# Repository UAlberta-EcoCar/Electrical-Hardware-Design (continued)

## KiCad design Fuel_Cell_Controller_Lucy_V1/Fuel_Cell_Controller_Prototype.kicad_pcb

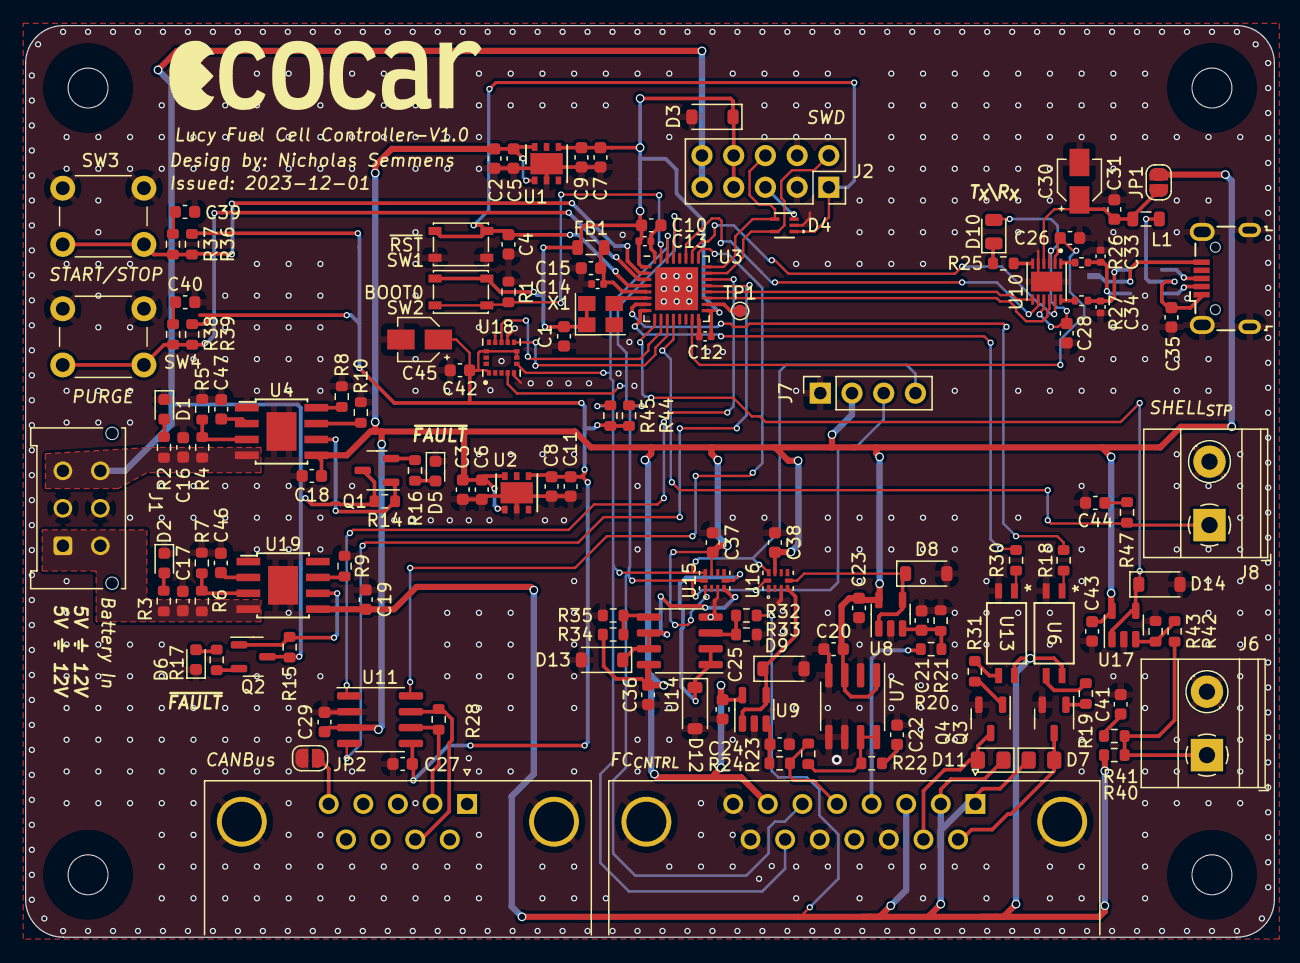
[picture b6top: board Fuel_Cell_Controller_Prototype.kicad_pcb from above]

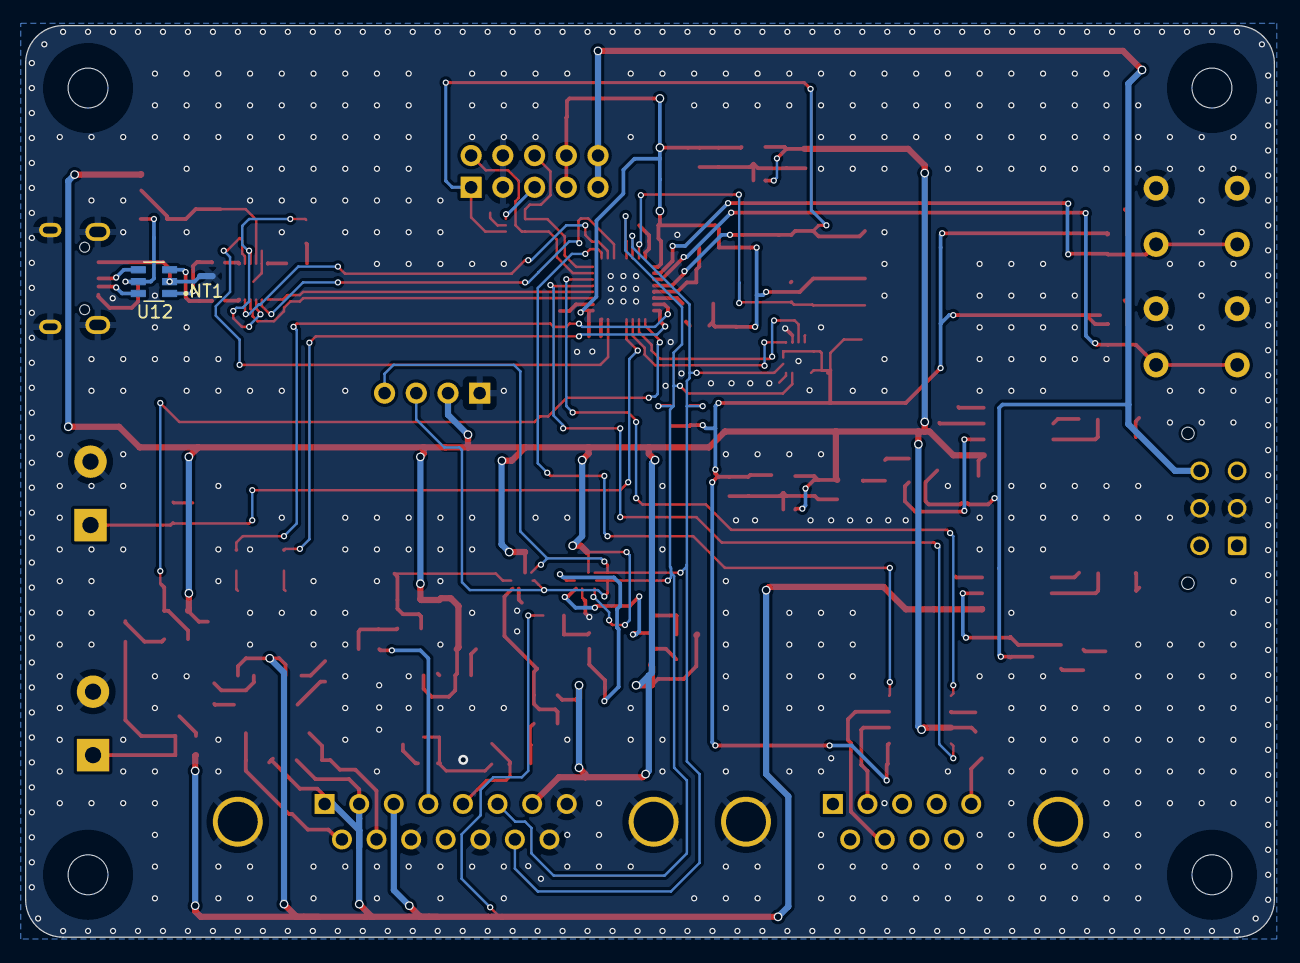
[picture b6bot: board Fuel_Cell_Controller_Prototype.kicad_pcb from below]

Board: 2 copper layers, 100.0 x 73.0 mm, 148 parts (2 on the bottom side), 89 nets.

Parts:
C1, C4, C5, C6, C9, C11, C23, C25, C26, C27, C28, C29, C31, C35, C36, C37, C38, C42, C43: 100n; C_0603_1608Metric
C2, C3, C7, C8, C15, C16, C17, C18, C19, C24: 1u; C_0603_1608Metric
C10: 4u7; C_0603_1608Metric
C12, C13, C14: 100n; C_0402_1005Metric
C20, C22, C39, C40, C41, C44: 2u2; C_0603_1608Metric
C21: 0u33; C_0603_1608Metric
C30: 4u7; CP_Elec_3x5.3
C33, C34: 47p; C_0402_1005Metric
C45: 10u; CP_Elec_3x5.3
C46, C47: 2n2; C_0603_1608Metric
D1, D2: BLUE; LED_0603_1608Metric
D3, D8, D9, D12, D13, D14: MMSZ5226B-7-F; D_SOD_123_M
D4: ESDALC6V1P5
D5, D6: EMERALD; LED_0603_1608Metric
D7, D11: SD0805S020S1R0; D_0805_2012Metric_Pad1.15x1.40mm_HandSolder
D10: PINK; LED_0805_2012Metric
Display 128x64 0.96" I2C: Display_128x64; Display_128x64_096_I2C
FB1: 600R; L_0805_2012Metric
H1, H2, H3, H4: MountingHole; MountingHole_3.2mm_M3
J1: STD_PWR_HEADER
J2: Conn_02x05_Odd_Even; PinSocket_2x05_P2.54mm_Vertical
J3: DE9_Receptacle; DSUB-9_Female_Horizontal_P2.77x2.84mm_EdgePinOffset7.70mm_H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
J4: DA15_Receptacle_MountingHoles; DSUB-15_Female_Horizontal_P2.77x2.84mm_EdgePinOffset7.70mm_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
J5: USB_B_Micro; USB_Micro-B_Wuerth_629105150521
J6, J8: Screw_Terminal_01x02; TerminalBlock_Phoenix_MKDS-1,5-2-5.08_1x02_P5.08mm_Horizont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
J7: OLED; PinSocket_1x04_P2.54mm_Vertical
JP1, JP2: SolderJumper_2_Open; SolderJumper-2_P1.3mm_Open_RoundedPad1.0x1.5mm
L1: 600R/0.5A; L_0805_2012Metric
NT1: NetTie_2; NetTie-2_SMD_Pad0.5mm
Q1, Q2: SI2302A-TPMSCT-ND; SOT-23-3
Q3, Q4: FMMT491ATA; SOT-23-3
R1, R5, R7, R24, R36, R37, R38, R39, R40, R41, R47: 10k; R_0603_1608Metric
R2, R16, R17: 270; R_0603_1608Metric
R3, R43: 820; R_0603_1608Metric
R4: 11k; R_0603_1608Metric
R6: 900; R_0603_1608Metric
R8: 400k; R_0603_1608Metric
R9, R10: 1k; R_0603_1608Metric
R14, R15, R23: 100k; R_0603_1608Metric
R18, R30: 422; R_0603_1608Metric
R19, R31: 249; R_0603_1608Metric
R20: 6.8k; R_0603_1608Metric
R21, R33, R34, R35: 13k; R_0603_1608Metric
R22, R25: 51; R_0603_1608Metric
R26, R27: 33; R_0402_1005Metric
R28: 120; R_0603_1608Metric
R32: 51k; R_0603_1608Metric
R42: 2.2k; R_0603_1608Metric
R44, R45: 4.7k; R_0603_1608Metric
SW1, SW2: PTS815 SJM 250 SMTR LFS; SW_SPST_PTS810
SW3, SW4: SW_PUSH_6mm_H5mm
TP1: MCO; TestPoint_Pad_D1.0mm
U1, U2: LD39050PU33R; DFN-6-1EP_3x3mm_P0.95mm_EP1.7x2.6mm
U3: STM32L432KCUx; QFN-32-1EP_5x5mm_P0.5mm_EP3.45x3.45mm
U4, U19: TPS259621; TI_SO-PowerPAD-8
U6, U13: EL3H7(B)(TA)-VG; SOIC_BTA-VG_EVS
U7: MCP1501-33E/SN; SOIC-8_3.9x4.9mm_P1.27mm
U8, U9, U17: AD8603; TSOT-23-5
U10: FT234XD-R; SON45P300X300X80-13N
U11: MCP2542FD-E/SN; SOIC-8_3.9x4.9mm_P1.27mm
U12: USBLC6-2SC6
U14: MCP602-E/SN; SOIC-8_3.9x4.9mm_P1.27mm
U15, U16: ADS1115IRUGR; IC_ADS1115IRUGR
U18: LIS3DHTR; XDCR_LIS3DHTR
X1: OXETDLJANF-8MHZ; Crystal_SMD_3225-4Pin_3.2x2.5mm

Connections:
+3V3: C8.2, C11.2, C27.1, C42.2, C45.1, R37.2, R38.2, R44.2, R45.2, U2.4 (VO), U11.5 (VIO), U18.1 (VDD_IO), U18.7 (SDO/SA0), U18.8 (CS), U18.14 (VDD)
+5V: C2.2, C3.2, C5.2, C6.2, C18.2, C20.1, C23.2, C25.2, C29.2, C36.2, C37.2, C38.2, C43.2, J4.7, J7.2, JP1.2 (B), R34.1, U1.1 (EN), U1.6 (VI), U2.1 (EN), U2.6 (VI), U4.5 (OUT), U7.1 (VDD), U7.3 (~SHDN), U8.5 (V+), U9.5 (V+), U11.3 (VDD), U14.8 (V+), U15.1 (ADDR), U15.8 (VDD), U16.8 (VDD), U17.5 (V+)
+12V: C19.2, D7.1 (K), D11.1 (K), J4.1, J4.2, J4.3, R32.1, R40.1, U6.4, U13.4, U19.5 (OUT)
/BOOT0: R1.2, SW2.1, U3.31 (PH3)
/BTN_{1}: R36.2, R37.1, SW3.2, U3.2 (PC14)
/BTN_{2}: R38.1, R39.2, SW4.2, U3.3 (PC15)
/FLT_{5}: Q1.1 (G), R14.1, U4.6 (~FAULT)
/FLT_{12}: Q2.1 (G), R15.1, U19.6 (~FAULT)
/IO /BTN_{RTN}: J6.1, R40.2, R41.1, R42.2
/IO /CAN_H: J3.7, R28.2, U11.7 (CANH)
/IO /CAN_L: J3.2, R28.1, U11.6 (CANL)
/IO /D+: J5.3 (D+), U12.4
/IO /D-: J5.2 (D-), U12.6
/IO /DM: C33.1, R26.2, U12.1
/IO /DP: C34.1, R27.2, U12.3
/IO /FC_{TEMP}: D9.1, U9.1, U9.4 (-), U16.4 (AIN0)
/IO /GND_{1}: J5.5 (GND), NT1.2, U12.2
/IO /H2_{PRS}: D8.1, U8.1, U8.4 (-), U16.5 (AIN1)
/IO /PA0: U3.6 (PA0), X1.3 (OUT)
/IO /PA1: R18.2, U3.7 (PA1)
/IO /PA2: R30.2, U3.8 (PA2)
/IO /PA3: D14.1, U3.9 (PA3), U17.1, U17.4 (-)
/IO /PA4: U3.10 (PA4), U18.11 (INT1)
/IO /PA5: U3.11 (PA5), U18.9 (INT2)
/IO /PA6: J8.1, R47.1, U3.12 (PA6)
/IO /PA8: TP1.1, U3.18 (PA8)
/IO /PA9: U3.19 (PA9), U10.10 (RXD)
/IO /PA10: U3.20 (PA10), U10.7 (TXD)
/IO /PA11: U3.21 (PA11), U11.4 (RXD)
/IO /PA12: U3.22 (PA12), U11.1 (TXD)
/IO /PA13: D4.5, J2.2, U3.23 (PA13)
/IO /PA14: D4.4, J2.6, U3.24 (PA14)
/IO /PA15: U3.25 (PA15), U11.8 (STBY)
/IO /PB1: C26.2, U3.15 (PB1), U10.2 (~RESET#)
/IO /PB3: U3.26 (PB3), U10.11 (CTS#)
/IO /PB4: U3.27 (PB4), U10.8 (RTS#)
/IO /PB6: J4.6, J7.3, R44.1, U3.29 (PB6), U15.10 (SCL), U16.10 (SCL), U18.4 (SCL/SPC)
/IO /PB7: J4.14, J7.4, R45.1, U3.30 (PB7), U15.9 (SDA), U16.9 (SDA), U18.6 (SDA/SDI/SDO)
/IO /PRESSURE_SIG: J4.4, R20.2
/IO /PURGE_RTN: D11.2 (A), J4.10, Q4.3 (C)
/IO /Purge_Valve_Switch/V_{E}: R31.1, U13.3
/IO /SHIELD: J3.5, JP2.2 (B)
/IO /SUPPLY_RTN: D7.2 (A), J4.9, Q3.3 (C)
/IO /Supply_Valve_Switch/V_{E}: R19.1, U6.3
/IO /THERM_{VREF}: J4.5, R23.2, R24.2
/IO /VCCIO: C28.1, D10.2 (A), U10.3 (3V3OUT), U10.9 (VCCIO)
/IO /V_{BUS}: C35.1, J5.1 (VBUS), L1.2, U12.5
/MCU_3V3: C1.1, C7.2, C9.2, C10.1, C12.1, C13.1, D3.1, FB1.1, J2.7, J2.8, SW2.2, U1.4 (VO), U3.1 (VDD), U3.17 (VDD), X1.1 (Tri-State), X1.4 (VDD)
/On-Board Sensors/5V_{REF}: D13.1, U14.6 (-), U14.7, U15.4 (AIN0)
/On-Board Sensors/12V_{REF}: D12.1, U14.1, U14.2 (-), U15.5 (AIN1)
/SW_{IM}: D4.3, J2.5
/~RST: C4.1, D4.1, J2.1, SW1.2, U3.4 (NRST)
GNDA: C1.2, C2.1, C3.1, C4.2, C5.1, C6.1, C7.1, C8.1, C9.1, C10.2, C11.1, C12.2, C13.2, C14.2, C15.2, C16.1, C17.1, C18.1, C19.1, C20.2, C21.2, C22.2, C23.1, C24.2, C25.1, C26.1, C27.2, C28.2, C29.1, C30.2, C31.2, C33.2, C34.2, C35.2, C36.1, C37.1, C38.1, C39.2, C40.2, C41.2, C42.1, C43.1, C44.2, C45.2, C46.1, C47.1, D1.1 (K), D2.1 (K), D3.2, D4.2, D5.1 (K), D6.1 (K), D8.2, D9.2, D12.2, D13.2, D14.2, J1.2 (GND), J1.5 (GND), J2.3, J2.4, J3.0 (PAD), J4.0 (PAD), J4.8, J4.11 (P111), J4.13, J4.15, J5.6 (Shield), J6.2, J7.1, J8.2, JP2.1 (A), NT1.1, Q3.2 (E), Q4.2 (E), R1.1, R5.1, R7.1, R8.1, R9.1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
unnamed: C22.1, R22.2
unnamed: C39.1, R36.1
unnamed: C40.1, R39.1
unnamed: C41.1, R41.2
unnamed: C44.1, R47.2
unnamed: D1.2 (A), R2.1
unnamed: D2.2 (A), R3.1
unnamed: D5.2 (A), R16.1
unnamed: D6.2 (A), R17.1
unnamed: D10.1 (K), R25.1
unnamed: C30.1, C31.1, JP1.1 (A), L1.1, U10.4 (VCC)
unnamed: Q1.2 (S), R16.2
unnamed: Q2.2 (S), R17.2
unnamed: Q3.1 (B), R19.2
unnamed: Q4.1 (B), R31.2
unnamed: R18.1, U6.1
unnamed: R30.1, U13.1
unnamed: C14.1, C15.1, FB1.2, U3.5 (VDDA)
unnamed: R4.1, R5.2, U4.3 (EN/UVLO)
unnamed: R10.2, U4.7 (ILM)
unnamed: R8.2, U4.8 (OVLO)
unnamed: C47.2, U4.2 (dV/dT)
unnamed: R22.1, R23.1, U7.7 (OUT), U7.8 (FB)
unnamed: C21.1, R20.1, R21.1, U8.3 (+)
unnamed: C24.1, R24.1, U9.3 (+)
unnamed: R25.2, U10.6 (CBUS0)
unnamed: R26.1, U10.1 (USBDM)
unnamed: R27.1, U10.12 (USBDP)
unnamed: R32.2, R33.1, U14.3 (+)
unnamed: R34.2, R35.1, U14.5 (+)
unnamed: R42.1, R43.1, U17.3 (+)
unnamed: R6.1, R7.2, U19.3 (EN/UVLO)
unnamed: R9.2, U19.7 (ILM)
unnamed: C46.2, U19.2 (dV/dT)
UNPROTECTED_5V: C16.2, J1.3 (5V), J1.6 (5V), J2.9, J2.10, Q1.3 (D), Q2.3 (D), R2.2, R4.2, R14.2, R15.2, U4.4 (IN)
UNPROTECTED_12V: C17.2, J1.1 (12V), J1.4 (12V), R3.2, R6.2, U19.4 (IN)

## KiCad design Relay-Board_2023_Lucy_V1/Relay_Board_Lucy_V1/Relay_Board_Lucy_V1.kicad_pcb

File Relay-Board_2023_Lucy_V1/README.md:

#I'm not quite sure how these documents work yet but im excited to find out

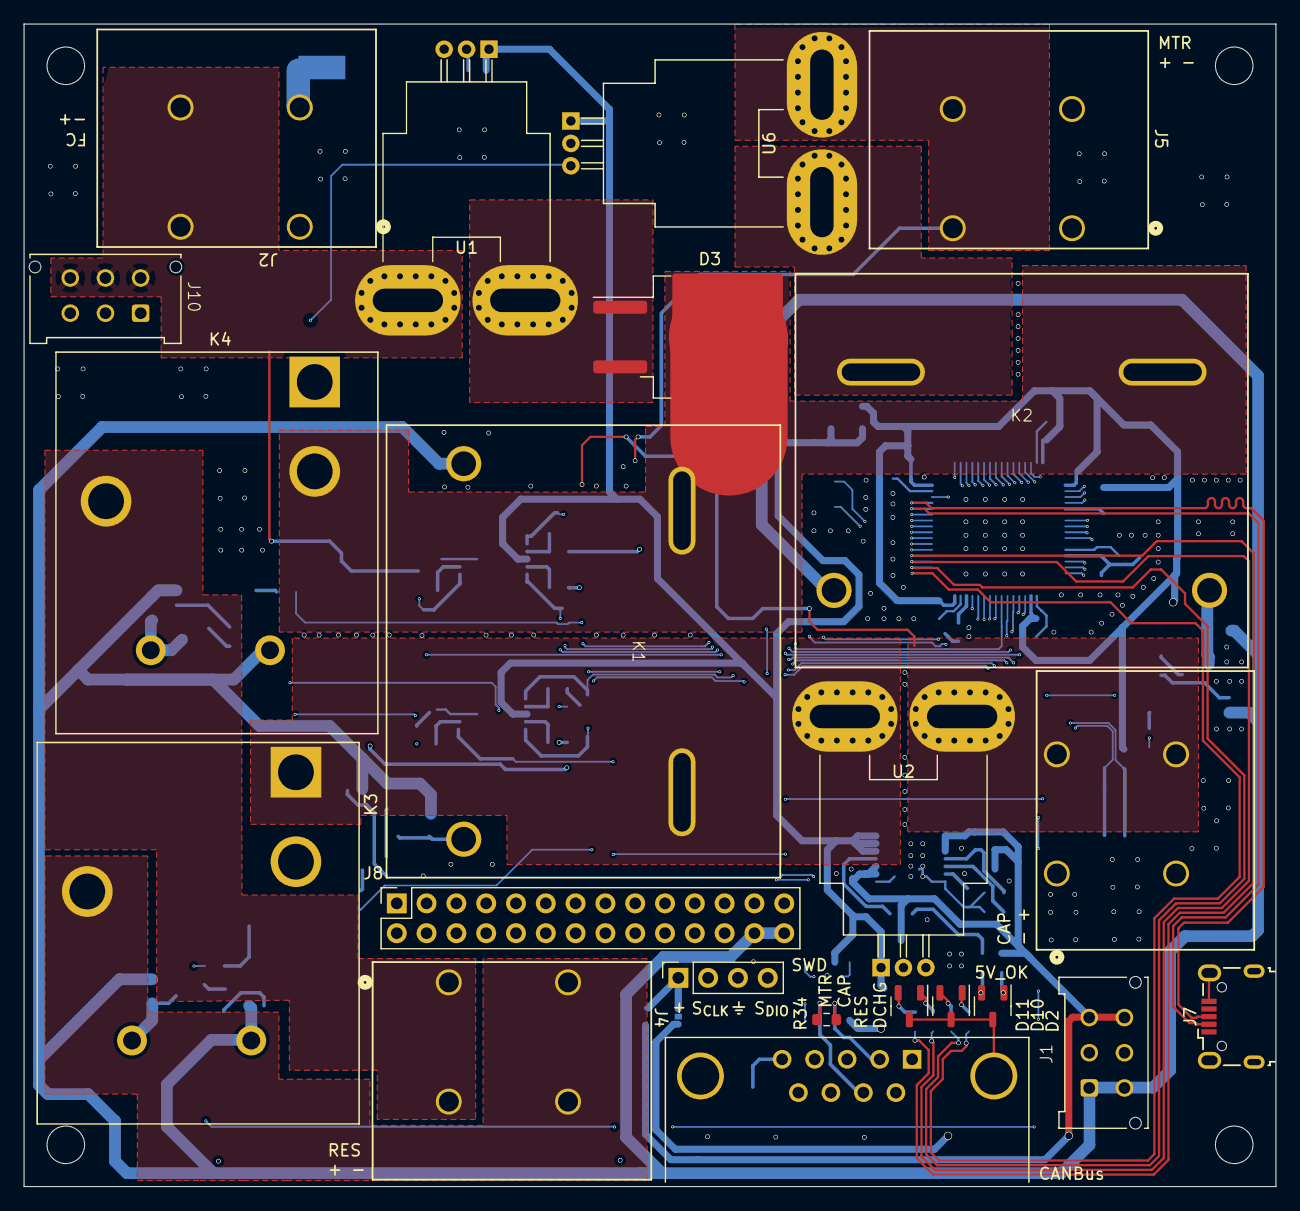
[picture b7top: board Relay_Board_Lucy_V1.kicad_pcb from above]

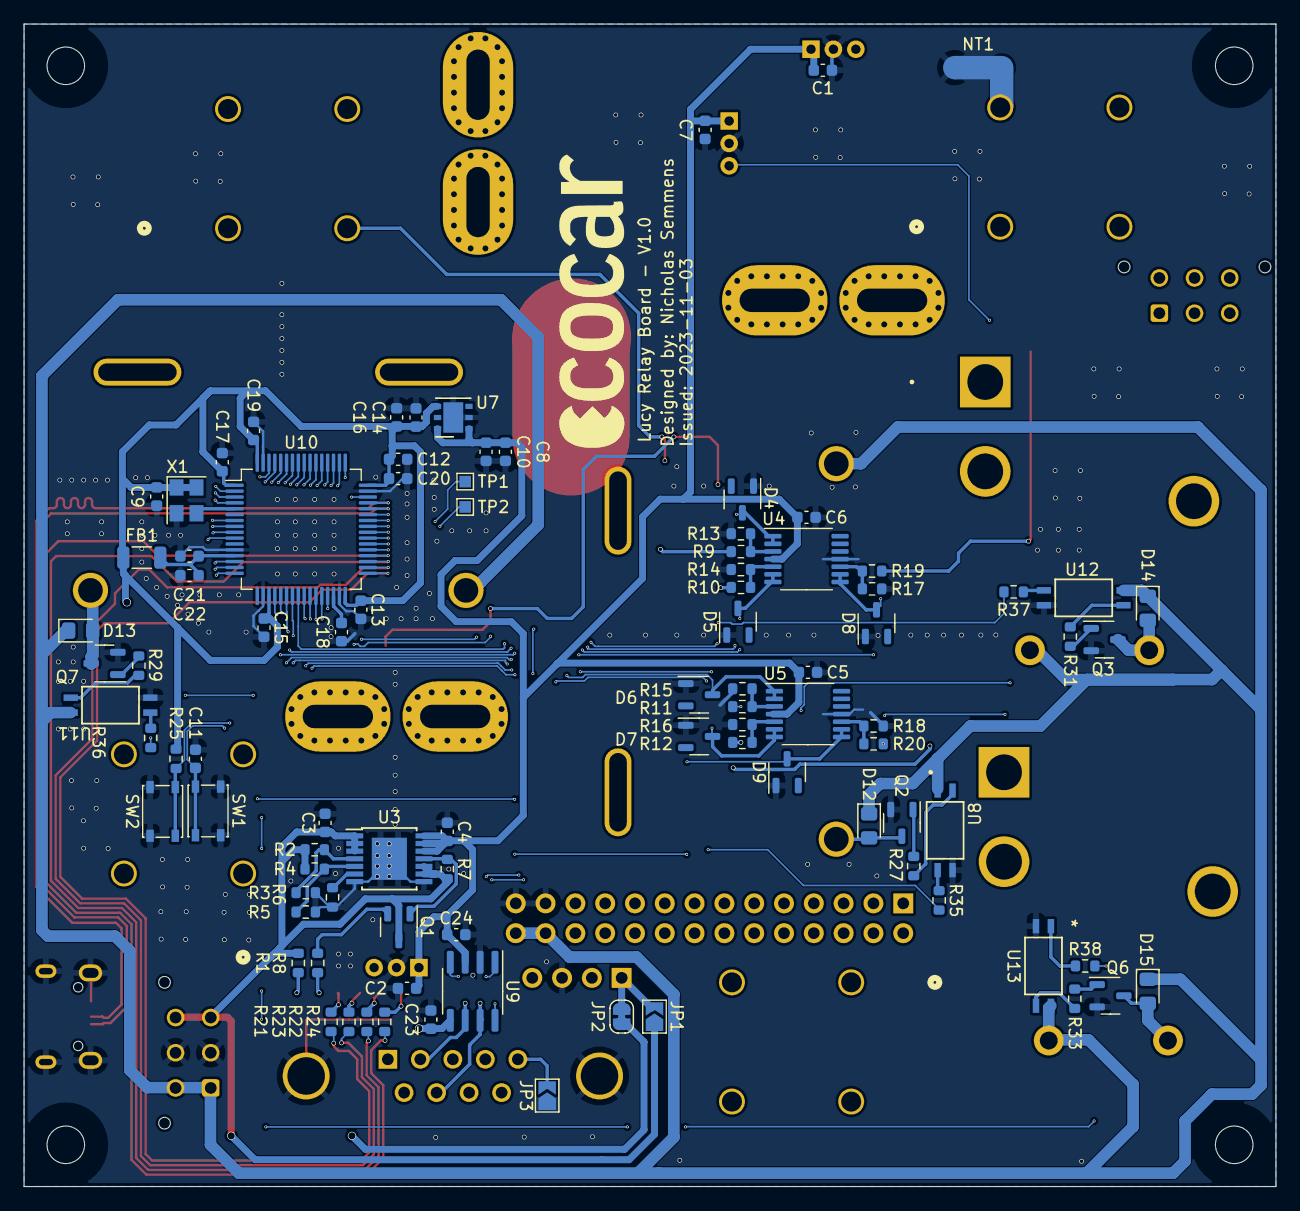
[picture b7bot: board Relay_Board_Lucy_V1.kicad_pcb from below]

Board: 4 copper layers, 106.7 x 99.1 mm, 118 parts (92 on the bottom side), 106 nets.

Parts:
C1, C2, C5, C6, C7, C9, C10, C11, C13, C15, C16, C17, C19, C20, C21, C23, C24: 100n; C_0603_1608Metric
C3, C4, C8, C14, C22: 1u; C_0603_1608Metric
C12, C18: 4u7; C_0603_1608Metric
D2, D10, D11: AM23ESGW; SOT-23-3
D3: STPS5045SG-TR; TO-263-2
D4, D5, D6, D7, D8, D9: BZX84-C3V3,215; SOT-23-3
D12, D13, D14, D15: SD0805S020S1R0; D_0805_2012Metric_Pad1.15x1.40mm_HandSolder
FB1: 300R; L_1206_3216Metric
H1, H2, H3, H4: MountingHole; MountingHole_3.2mm_M3
J1, J10: STD_PWR_HEADER
J2, J3, J4, J5: VP0265540000G; CONN_VP0265x4xxxxG_AMP
J6: SWD_HEADER; PinSocket_1x04_P2.54mm_Vertical
J7: USB_B_Micro; USB_Micro-B_Wuerth_629105150521
J8: Conn_02x14_Top_Bottom; PinSocket_2x14_P2.54mm_Vertical
J9: DE9_Receptacle_MountingHoles; DSUB-9_Female_Horizontal_P2.77x2.84mm_EdgePinOffset7.70mm_H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
JP1, JP3: SolderJumper_2_Open; SolderJumper-2_P1.3mm_Open_TrianglePad1.0x1.5mm
JP2: SolderJumper_2_Bridged; SolderJumper-2_P1.3mm_Bridged_RoundedPad1.0x1.5mm
K1, K2: HE1AN-P-DC12V-Y5
K3, K4: J115F11CH12VDCS61.5
NT1: NetTie_2; NetTie-2_SMD_Pad2.0mm
Q1: SI2302A-TPMSCT-ND; SOT-23-3
Q2, Q3, Q6, Q7: FMMT491ATA; SOT-23-3
R1: 160; R_0603_1608Metric
R2, R4: 2.2M; R_0603_1608Metric
R3: 953k; R_0603_1608Metric
R5: 549k; R_0603_1608Metric
R6: 11.5k; R_0603_1608Metric
R7, R11, R12, R20: 100k; R_0603_1608Metric
R8: 150; R_0603_1608Metric
R9, R10, R19: 417k; R_0603_1608Metric
R13, R14, R17: 50k; R_0603_1608Metric
R15, R16, R18: 200k; R_0603_1608Metric
R21, R23: 140; R_0603_1608Metric
R22, R24: 130; R_0603_1608Metric
R25: 10k; R_0603_1608Metric
R27, R29, R31, R33: 246; R_0603_1608Metric
R34: 120; R_0603_1608Metric
R35, R36, R37, R38: 422; R_0603_1608Metric
SW1, SW2: PTS815 SJM 250 SMTR LFS; SW_SPST_PTS810
TP1, TP2: TestPoint_Alt; TestPoint_Pad_1.0x1.0mm
U1, U6: ACS770LCB-050U-PFF; Allegro_CB_PFF_Adjusted
U2: ACS770LCB-050B-PFF; Allegro_CB_PFF_Adjusted
U3: MAX14572; TSSOP-14-1EP_4.4x5mm_P0.65mm
U4, U5: TSV914IPT; TSSOP-14_4.4x5mm_P0.65mm
U7: LD39050PU33R; DFN-6-1EP_3x3mm_P0.95mm_EP1.7x2.6mm
U8, U11, U12, U13: EL3H7(B)(TA)-VG; SOIC_BTA-VG_EVS
U9: MCP2542FD-E/SN; SOIC-8_3.9x4.9mm_P1.27mm
U10: STM32F446RETx; LQFP-64_10x10mm_P0.5mm
X1: OXETDLJANF-8MHZ; Crystal_SMD_3225-4Pin_3.2x2.5mm

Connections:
+3.3VA: C21.1, C22.1, FB1.2, U10.13 (VDDA)
+3V3: C9.1, C12.1, C13.1, C14.1, C15.1, C16.1, C17.1, C19.1, C20.1, C23.1, FB1.1, JP2.1 (A), R25.1, U7.4 (VO), U9.5 (VIO), U10.1 (VBAT), U10.19 (VDD), U10.32 (VDD), U10.48 (VDD), U10.64 (VDD), X1.1 (Tri-State), X1.4 (VDD)
+5V: C1.1, C2.1, C4.2, C5.1, C6.1, C7.1, C8.1, C10.1, C24.2, U1.1 (VCC), U2.1 (VCC), U3.12 (OUT), U3.13 (OUT), U3.14 (OUT), U4.4 (VCC+), U5.4 (VCC+), U6.1 (VCC), U7.1 (EN), U7.6 (VI), U9.3 (VDD)
/CAP Relay/V_{E}: R27.1, U8.3
/CAP+: J3.3, J3.4, R10.2, U2.4 (IP+)
/CAP_CURR: R12.2, U2.3 (VIOUT)
/FC+: J2.3, J2.4, J10.4 (12V), J10.5 (GND), J10.6 (5V), R19.2, U1.4 (IP+)
/FC_CURR: R11.2, U1.3 (VIOUT)
/MAIN_POWER_BUS: D3.2 (K), K1.1 (IN-), K2.4 (IN+), K4.2
/MCU/BOOT0: R25.2, SW2.2, U10.60 (BOOT0)
/MCU/CAN_H: J9.7, R34.2, U9.7 (CANH)
/MCU/CAN_L: J9.2, R34.1, U9.6 (CANL)
/MCU/CLK: U10.5 (PH0), X1.3 (OUT)
/MCU/PA0: J8.4, U10.14 (PA0)
/MCU/PA1: J8.2, U10.15 (PA1)
/MCU/PA2: J8.1, U10.16 (PA2)
/MCU/PA4: D8.3 (K), U4.8 (OUT3), U4.9 (IN3-), U10.20 (PA4)
/MCU/PA5: D9.3 (K), U5.8 (OUT3), U5.9 (IN3-), U10.21 (PA5)
/MCU/PA6: D5.3 (K), U4.6 (IN2-), U4.7 (OUT2), U10.22 (PA6)
/MCU/PA7: D7.3 (K), U5.6 (IN2-), U5.7 (OUT2), U10.23 (PA7)
/MCU/PA8: TP1.1, U10.41 (PA8)
/MCU/PA9: J8.21, U10.42 (PA9)
/MCU/PA10: J8.24, U10.43 (PA10)
/MCU/PA13: J6.4, U10.46 (PA13)
/MCU/PA14: J6.2, U10.49 (PA14)
/MCU/PA15: J8.17, U10.50 (PA15)
/MCU/PB0: R38.2, U10.26 (PB0)
/MCU/PB1: R37.2, U10.27 (PB1)
/MCU/PB2: R35.2, U10.28 (PB2)
/MCU/PB3: J8.14, U10.55 (PB3)
/MCU/PB4: J8.11, U10.56 (PB4)
/MCU/PB5: J8.12, U10.57 (PB5)
/MCU/PB6: J8.9, U10.58 (PB6)
/MCU/PB7: U9.8 (STBY), U10.59 (PB7)
/MCU/PB8: U9.4 (RXD), U10.61 (PB8)
/MCU/PB9: U9.1 (TXD), U10.62 (PB9)
/MCU/PB10: R36.2, U10.29 (PB10)
/MCU/PB12: R21.1, U10.33 (PB12)
/MCU/PB13: R22.2, U10.34 (PB13)
/MCU/PB14: R23.1, U10.35 (PB14)
/MCU/PB15: R24.2, U10.36 (PB15)
/MCU/PC0: J8.5, U10.8 (PC0)
/MCU/PC1: J8.6, U10.9 (PC1)
/MCU/PC2: J8.3, U10.10 (PC2)
/MCU/PC4: D4.3 (K), U4.1 (OUT1), U4.2 (IN1-), U10.24 (PC4)
/MCU/PC5: D6.3 (K), U5.1 (OUT1), U5.2 (IN1-), U10.25 (PC5)
/MCU/PC6: J8.20, U10.37 (PC6)
/MCU/PC7: J8.19, U10.38 (PC7)
/MCU/PC8: J8.22, U10.39 (PC8)
/MCU/PC9: TP2.1, U10.40 (PC9)
/MCU/PC10: J8.18, U10.51 (PC10)
/MCU/PC11: J8.15, U10.52 (PC11)
/MCU/PC12: J8.16, U10.53 (PC12)
/MCU/PC13: J8.10, U10.2 (PC13)
/MCU/PC14: J8.7, U10.3 (PC14)
/MCU/PC15: J8.8, U10.4 (PC15)
/MCU/PD2: J8.13, U10.54 (PD2)
/MCU/SHIELD: J9.5, JP3.2 (B)
/MCU/USB_D+: J7.3 (D+), U10.45 (PA12)
/MCU/USB_D-: J7.2 (D-), U10.44 (PA11)
/MCU/~RST: C11.1, SW1.2, U10.7 (NRST)
/MOTOR Relay/HIGH_VOLT_OUT: K2.1 (IN-), U6.4 (IP+)
/MOTOR Relay/V_{E}: R29.1, U11.3
/MOTOR+: J5.3, J5.4, R9.2, U6.5 (IP-)
/MOTOR_CURR: R20.2, U6.3 (VIOUT)
/RES+: J4.1, J4.2, K4.5
/RES-: J4.3, J4.4, K3.5
/TO_CAPS: K1.4 (IN+), K3.1, U2.5 (IP-)
/TO_LED: D2.1 (A1), R1.1
GNDA: C1.2, C2.2, C3.2, C4.1, C5.2, C6.2, C7.2, C8.2, C9.2, C10.2, C11.2, C12.2, C13.2, C14.2, C15.2, C16.2, C17.2, C18.2, C19.2, C20.2, C21.2, C22.2, C23.2, C24.1, D2.3 (K), D4.1 (A), D5.1 (A), D6.1 (A), D7.1 (A), D8.1 (A), D9.1 (A), D10.3 (K), D11.3 (K), J1.2 (GND), J1.5 (GND), J6.3, J7.5 (GND), J7.6 (Shield), J8.25, J8.27, J9.0 (PAD), JP3.1 (A), NT1.1, Q2.2 (E), Q3.2 (E), Q6.2 (E), Q7.2 (E), R3.1, R5.1, R6.1, R13.2, R14.2, R15.2, R16.2, R17.2, R18.2, SW1.1, SW2.1, U1.2 (GND), U2.2 (GND), U3.7 (GND), U3.8 (~HVEN), U3.15 (EP), U4.11 (VCC-), U5.11 (VCC-), U6.2 (GND), U7.2 (GND), U7.7 (GND), U8.2, U9.2 (VSS), U10.12 (VSSA), U10.18 (VSS), U10.31 (VSS), U10.47 (VSS), U10.63 (VSS), U11.2, U12.2, U13.2, X1.2 (GND)
GNDPWR: J2.1, J2.2, J3.1, J3.2, J5.1, J5.2, J10.1 (12V), J10.2 (GND), J10.3 (5V), K3.2, K4.1, NT1.2
unnamed: D2.2 (A2), R8.1
unnamed: D10.1 (A1), R21.2
unnamed: D10.2 (A2), R22.1
unnamed: D11.1 (A1), R23.2
unnamed: D11.2 (A2), R24.1
unnamed: D12.2 (A), K1.5 (CNTRL-), Q2.3 (C)
unnamed: D13.2 (A), K2.5 (CNTRL-), Q7.3 (C)
unnamed: D14.2 (A), K4.4, Q3.3 (C)
unnamed: D15.2 (A), K3.4, Q6.3 (C)
unnamed: J6.1, JP1.2 (B), JP2.2 (B)
unnamed: Q1.1 (G), R7.1, U3.11 (~FLAG)
unnamed: Q1.2 (S), R8.2
unnamed: Q2.1 (B), R27.2
unnamed: Q3.1 (B), R31.2
unnamed: Q6.1 (B), R33.2
unnamed: Q7.1 (B), R29.2
unnamed: R31.1, U12.3
unnamed: R33.1, U13.3
unnamed: R35.1, U8.1
unnamed: R36.1, U11.1
unnamed: R37.1, U12.1
unnamed: R38.1, U13.1
unnamed: D3.1 (A), D3.3 (A), U1.5 (IP-)
unnamed: R4.1, R5.2, U3.5 (OVLO)
unnamed: R6.2, U3.6 (SETI)
unnamed: R2.1, R3.2, U3.4 (UVLO)
unnamed: R9.1, R13.1, U4.3 (IN1+)
unnamed: R10.1, R14.1, U4.5 (IN2+)
unnamed: R17.1, R19.1, U4.10 (IN3+)
unnamed: R11.1, R15.1, U5.3 (IN1+)
unnamed: R12.1, R16.1, U5.5 (IN2+)
unnamed: R18.1, R20.1, U5.10 (IN3+)
unnamed: C18.1, U10.30 (VCAP_1)
UNPROTECTED_5V: C3.1, J1.3 (5V), J1.6 (5V), JP1.1 (A), Q1.3 (D), R1.2, R2.2, R4.2, R7.2, U3.1 (IN), U3.2 (IN), U3.3 (IN), U3.9 (RIEN), U3.10 (EN)
UNPROTECTED_12V: D12.1 (K), D13.1 (K), D14.1 (K), D15.1 (K), J1.1 (12V), J1.4 (12V), J8.26, J8.28, K1.6 (CNTRL+), K2.6 (CNTRL+), K3.3, K4.3, U8.4, U11.4, U12.4, U13.4

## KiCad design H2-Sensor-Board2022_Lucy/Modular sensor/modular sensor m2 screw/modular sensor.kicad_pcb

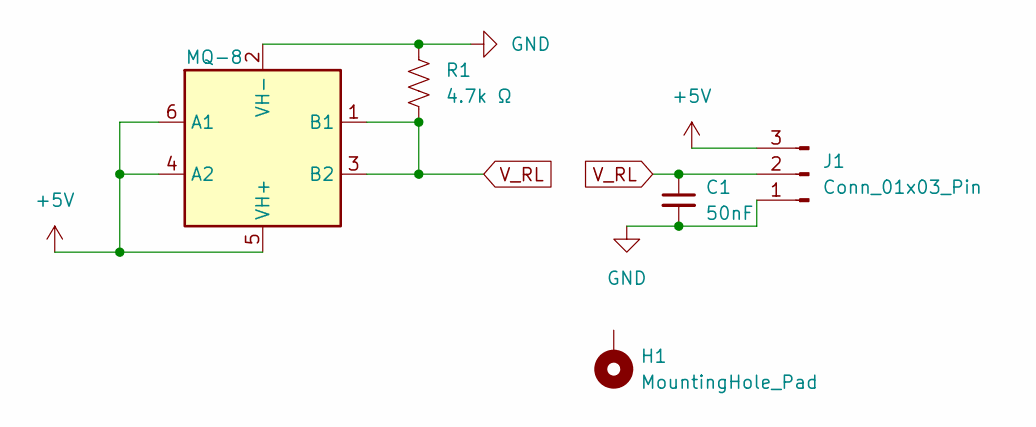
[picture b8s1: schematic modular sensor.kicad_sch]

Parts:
C1: 50nF; C_1206_3216Metric_Pad1.33x1.80mm_HandSolder; LCSC C9807
H1: MountingHole_Pad; MountingHole_2.7mm_M2.5_Pad_Via
J1: Conn_01x03_Pin; PinHeader_1x03_P2.54mm_Vertical; LCSC C49257
MQ-8: MQ-8
R1: 4.7k Ω; R_1206_3216Metric_Pad1.30x1.75mm_HandSolder; LCSC C414910

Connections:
+5V: J1.3, MQ-8.4 (A2), MQ-8.5 (VH+), MQ-8.6 (A1)
GND: C1.2, J1.1, MQ-8.2 (VH-), R1.1
V_RL: C1.1, J1.2, MQ-8.1 (B1), MQ-8.3 (B2), R1.2

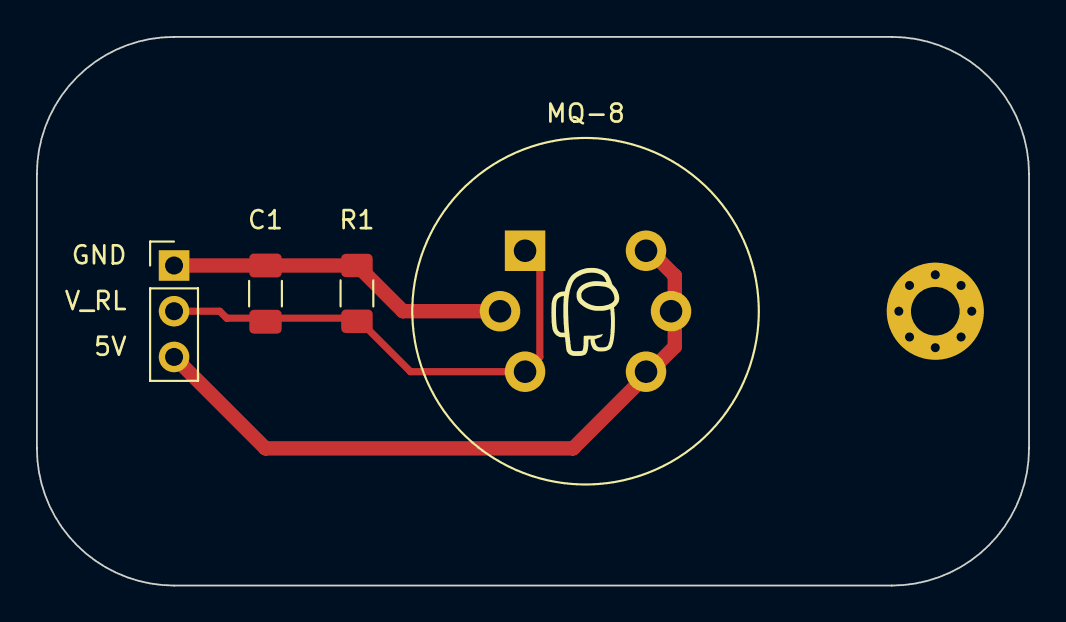
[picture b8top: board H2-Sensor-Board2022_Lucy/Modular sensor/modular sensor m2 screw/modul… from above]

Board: 2 copper layers, 55.1 x 30.5 mm, 5 parts (0 on the bottom side), 3 nets.

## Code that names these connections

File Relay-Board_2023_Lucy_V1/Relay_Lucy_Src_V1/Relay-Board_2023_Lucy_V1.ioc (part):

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Mcu.Name=STM32F446R(C-E)Tx
Mcu.Package=LQFP64
Mcu.UserName=STM32F446RETx
PA0-WKUP.GPIOParameters=GPIO_Label
PA0-WKUP.GPIO_Label=LED_OFF_STATE
PA0-WKUP.Signal=GPIO_Output
PA1.GPIOParameters=GPIO_Label
PA1.GPIO_Label=LED_CHARGE_STATE
PA1.Signal=GPIO_Output
PA11.Mode=Device_Only
PA11.Signal=USB_OTG_FS_DM
PA12.Mode=Device_Only
PA12.Signal=USB_OTG_FS_DP
PA13.Mode=Serial_Wire
PA13.Signal=SYS_JTMS-SWDIO
PA14.Mode=Serial_Wire
PA14.Signal=SYS_JTCK-SWCLK
PA2.GPIOParameters=GPIO_Label
PA2.GPIO_Label=LED_ON_STATE
PA2.Signal=GPIO_Output
PA4.GPIOParameters=GPIO_Label
PA4.GPIO_Label=FC_VOLT
PA4.Signal=ADCx_IN4
PA5.GPIOParameters=GPIO_Label
PA5.GPIO_Label=MOTOR_CURR
PA5.Signal=ADCx_IN5
PA6.GPIOParameters=GPIO_Label
PA6.GPIO_Label=CAP_VOLT
PA6.Signal=ADCx_IN6
PA7.GPIOParameters=GPIO_Label
PA7.GPIO_Label=CAP_CURR
PA7.Signal=ADCx_IN7
PA8.Mode=Clock-out-1
PA8.Signal=RCC_MCO_1
PB0.GPIOParameters=GPIO_Label
PB0.GPIO_Label=DSCHRGE_RELAY
PB0.Signal=GPIO_Output
PB1.GPIOParameters=GPIO_Label
PB1.GPIO_Label=RES_RELAY
PB1.Signal=GPIO_Output
PB10.GPIOParameters=GPIO_Label
PB10.GPIO_Label=MTR_RELAY
PB10.Signal=GPIO_Output
PB12.GPIOParameters=GPIO_Label
PB12.GPIO_Label=DSCHRGE_LED
PB12.Signal=GPIO_Output
PB13.GPIOParameters=GPIO_Label
PB13.GPIO_Label=RES_LED
PB13.Signal=GPIO_Output
PB14.GPIOParameters=GPIO_Label
PB14.GPIO_Label=MTR_LED
PB14.Signal=GPIO_Output
PB15.GPIOParameters=GPIO_Label
PB15.GPIO_Label=CAP_LED
PB15.Signal=GPIO_Output
PB2.GPIOParameters=GPIO_Label
PB2.GPIO_Label=CAP_RELAY
PB2.Signal=GPIO_Output
PB7.GPIOParameters=GPIO_Label
PB7.GPIO_Label=CAN_STBY
PB7.Signal=GPIO_Output
PB8.GPIOParameters=GPIO_PuPd
PB8.GPIO_PuPd=GPIO_PULLUP
PB8.Mode=CAN_Activate
PB8.Signal=CAN1_RX
PB9.GPIOParameters=GPIO_PuPd
PB9.GPIO_PuPd=GPIO_NOPULL
PB9.Mode=CAN_Activate
PB9.Signal=CAN1_TX
PC4.GPIOParameters=GPIO_Label
PC4.GPIO_Label=MTR_VOLT
PC4.Signal=ADCx_IN14
PC5.GPIOParameters=GPIO_Label
PC5.GPIO_Label=FC_CURR
PC5.Signal=ADCx_IN15
PC9.Mode=Clock-out-2
PC9.Signal=RCC_MCO_2
PH0-OSC_IN.Mode=HSE-External-Clock-Source
PH0-OSC_IN.Signal=RCC_OSC_IN
PH1-OSC_OUT.Mode=HSE-External-Clock-Source
PH1-OSC_OUT.Signal=RCC_OSC_OUT
RCC.HSE_VALUE=8000000
RCC.SYSCLKFreq_VALUE=180000000
RCC.SYSCLKSource=RCC_SYSCLKSOURCE_PLLCLK
board=custom

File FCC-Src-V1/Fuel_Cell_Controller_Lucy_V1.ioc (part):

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Mcu.Name=STM32L432K(B-C)Ux
Mcu.Package=UFQFPN32
Mcu.UserName=STM32L432KCUx
PA0.Mode=HSE-External-Clock-Source-for-LittleOrca
PA0.Signal=RCC_CK_IN
PA1.GPIOParameters=PinState,GPIO_PuPd,GPIO_Label
PA1.GPIO_Label=SUPPLY_VLVE
PA1.GPIO_PuPd=GPIO_PULLDOWN
PA1.PinState=GPIO_PIN_RESET
PA1.Signal=GPIO_Output
PA10.Mode=Asynchronous
PA10.Signal=USART1_RX
PA11.Mode=CAN_Activate
PA11.Signal=CAN1_RX
PA12.Mode=CAN_Activate
PA12.Signal=CAN1_TX
PA13\ (JTMS-SWDIO).Mode=Serial_Wire
PA13\ (JTMS-SWDIO).Signal=SYS_JTMS-SWDIO
PA14\ (JTCK-SWCLK).Mode=Serial_Wire
PA14\ (JTCK-SWCLK).Signal=SYS_JTCK-SWCLK
PA15\ (JTDI).GPIOParameters=GPIO_PuPd,GPIO_Label
PA15\ (JTDI).GPIO_Label=CAN_STBY
PA15\ (JTDI).GPIO_PuPd=GPIO_PULLDOWN
PA15\ (JTDI).Signal=GPIO_Output
PA2.GPIOParameters=GPIO_PuPd,GPIO_Label
PA2.GPIO_Label=PURGE_VLVE
PA2.GPIO_PuPd=GPIO_PULLDOWN
PA2.Signal=GPIO_Output
PA3.GPIOParameters=GPIO_PuPd,GPIO_Label,GPIO_ModeDefaultEXTI
PA3.GPIO_Label=EXT_STRT
PA3.GPIO_ModeDefaultEXTI=GPIO_MODE_IT_FALLING
PA3.GPIO_PuPd=GPIO_PULLUP
PA3.Signal=GPXTI3
PA4.GPIOParameters=GPIO_PuPd,GPIO_Label
PA4.GPIO_Label=ACC_INT1
PA4.GPIO_PuPd=GPIO_PULLDOWN
PA4.Signal=GPXTI4
PA5.GPIOParameters=GPIO_PuPd,GPIO_Label
PA5.GPIO_Label=ACC_INT2
PA5.GPIO_PuPd=GPIO_PULLDOWN
PA5.Signal=GPXTI5
PA6.GPIOParameters=GPIO_PuPd,GPIO_Label,GPIO_ModeDefaultEXTI
PA6.GPIO_Label=EXT_STOP
PA6.GPIO_ModeDefaultEXTI=GPIO_MODE_IT_FALLING
PA6.GPIO_PuPd=GPIO_PULLUP
PA6.Signal=GPXTI6
PA7.Signal=GPIO_Analog
PA8.Mode=Clock-out
PA8.Signal=RCC_MCO
PA9.Mode=Asynchronous
PA9.Signal=USART1_TX
PB0.Signal=GPIO_Analog
PB1.GPIOParameters=GPIO_PuPd,GPIO_Label
PB1.GPIO_Label=FTDI_NRST
PB1.GPIO_PuPd=GPIO_PULLUP
PB1.Signal=GPIO_Output
PB3\ (JTDO-TRACESWO).Mode=CTS_RTS
PB3\ (JTDO-TRACESWO).Signal=USART1_RTS
PB4\ (NJTRST).Mode=CTS_RTS
PB4\ (NJTRST).Signal=USART1_CTS
PB5.Signal=GPIO_Analog
PB6.Mode=I2C
PB6.Signal=I2C1_SCL
PB7.Mode=I2C
PB7.Signal=I2C1_SDA
PC14-OSC32_IN\ (PC14).GPIOParameters=GPIO_PuPd,GPIO_Label,GPIO_ModeDefaultEXTI
PC14-OSC32_IN\ (PC14).GPIO_Label=BRD_STRT
PC14-OSC32_IN\ (PC14).GPIO_ModeDefaultEXTI=GPIO_MODE_IT_FALLING
PC14-OSC32_IN\ (PC14).GPIO_PuPd=GPIO_PULLUP
PC14-OSC32_IN\ (PC14).Signal=GPXTI14
PC15-OSC32_OUT\ (PC15).GPIOParameters=GPIO_PuPd,GPIO_Label,GPIO_ModeDefaultEXTI
PC15-OSC32_OUT\ (PC15).GPIO_Label=BRD_PRGE
PC15-OSC32_OUT\ (PC15).GPIO_ModeDefaultEXTI=GPIO_MODE_IT_FALLING
PC15-OSC32_OUT\ (PC15).GPIO_PuPd=GPIO_PULLUP
PC15-OSC32_OUT\ (PC15).Signal=GPXTI15
PH3-BOOT0.Signal=GPIO_Analog
RCC.HSE_VALUE=8000000
RCC.SYSCLKFreq_VALUE=80000000
RCC.SYSCLKSource=RCC_SYSCLKSOURCE_PLLCLK
board=custom

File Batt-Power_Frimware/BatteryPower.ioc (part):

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Mcu.Name=STM32L432K(B-C)Ux
Mcu.Package=UFQFPN32
Mcu.UserName=STM32L432KCUx
PA0.Mode=HSE-External-Clock-Source-for-LittleOrca
PA0.Signal=RCC_CK_IN
PA1.GPIOParameters=GPIO_Label
PA1.GPIO_Label=ACD_Battery_Voltage
PA1.Signal=ADCx_IN6
PA11.GPIOParameters=GPIO_PuPd
PA11.GPIO_PuPd=GPIO_PULLUP
PA11.Mode=CAN_Activate
PA11.Signal=CAN1_RX
PA12.Mode=CAN_Activate
PA12.Signal=CAN1_TX
PA13\ (JTMS-SWDIO).Mode=Serial_Wire
PA13\ (JTMS-SWDIO).Signal=SYS_JTMS-SWDIO
PA14\ (JTCK-SWCLK).Mode=Serial_Wire
PA14\ (JTCK-SWCLK).Signal=SYS_JTCK-SWCLK
PA15\ (JTDI).GPIOParameters=GPIO_PuPd,GPIO_Label
PA15\ (JTDI).GPIO_Label=CAN_STBY
PA15\ (JTDI).GPIO_PuPd=GPIO_PULLDOWN
PA15\ (JTDI).Signal=GPIO_Input
PA2.GPIOParameters=GPIO_Label
PA2.GPIO_Label=Battery_Curr
PA2.Signal=ADCx_IN7
PA3.GPIOParameters=GPIO_Label
PA3.GPIO_Label=Current_Out_12V
PA3.Signal=ADCx_IN8
PA4.GPIOParameters=GPIO_Label
PA4.GPIO_Label=ADC_12V_Voltage_Out
PA4.Signal=ADCx_IN9
PA5.GPIOParameters=GPIO_Label
PA5.GPIO_Label=Current_Buck_12V
PA5.Signal=ADCx_IN10
PB3\ (JTDO-TRACESWO).GPIOParameters=GPIO_Label
PB3\ (JTDO-TRACESWO).GPIO_Label=GPLED1
PB3\ (JTDO-TRACESWO).Signal=GPIO_Output
PB4\ (NJTRST).GPIOParameters=GPIO_Label
PB4\ (NJTRST).GPIO_Label=GPLED2
PB4\ (NJTRST).Signal=GPIO_Output
PB5.GPIOParameters=GPIO_Label
PB5.GPIO_Label=GPLED3
PB5.Signal=GPIO_Output
PB6.Mode=Asynchronous
PB6.Signal=USART1_TX
PB7.Mode=Asynchronous
PB7.Signal=USART1_RX
PC14-OSC32_IN\ (PC14).Signal=GPXTI14
RCC.HSE_VALUE=8000000
RCC.SYSCLKFreq_VALUE=80000000
RCC.SYSCLKSource=RCC_SYSCLKSOURCE_PLLCLK
board=custom

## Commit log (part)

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2023-06-03 Added Sheet for power regulator
2023-06-03 Organization
2023-06-07 started on rf tranciever
2023-06-10 Added 6POS Molex connectors and started implementation of eFuses for 12v and 5V protection
2023-06-13 Made minor changes
2023-06-17 Kicad Conversion
2023-06-24 Add files via upload
    Relay Board Block Diagram from June 2023
2023-06-24 made a new folder, i will rename the stuff in the folder in the next commit
2023-06-24 made a new folder, need to rename the project
2023-06-24 im going to make a new project
2023-06-24 Conversion
2023-06-25 Name Change
2023-07-01 Added actual eFuses with parts that can be bought. Some work still needs to be done with the MOSFETS for the leds
2023-07-08 Done power
2023-07-09 Branch Cleanup
2023-07-09 Clean up
2023-07-15 Added all schmatics about to change LDO 1 to buck
2023-07-15 created the project
2023-07-17 Starting to add CAN infrastructure
2023-07-29 Pushing symbols and footprints library
2023-07-29 KiCad Update
2023-07-29 Added stiching vias
2023-07-30 started working on the board
2023-07-30 Added some more CAN supporting hardware
2023-08-03 Small Update
2023-08-12 Update - Mikael
2023-08-12 Added another 3.3V power supply to seperate from the MCU 3.3V ps
2023-08-14 MCU Pinout
    First Rev of MCU Pinout/setup
2023-08-14 New modular sensor pog 👌
    new modular sensor beta testing
2023-08-14 Added some notes for Mikael
2023-08-15 change
2023-08-15 Small diagram added for how we could do power outputs
2023-08-17 Adds MCU and DSUB connector for fan control.
2023-08-19 Lots of updates to microcontroller sheet and IO sheet
2023-08-20 Slight changes to CAN stuff
2023-08-21 Changes to the clock on the MCU
2023-08-21 Done
2023-08-26 Dunno what changes i made
2023-08-26 Revert "huh"
    This reverts commit 7bb3ffd8f300d735453e7bd9492734dd47e7a050.
2023-08-27 Pushing alot of changes and hopefully resolving previous problems
2023-08-27 added 3v3 5 and 7v power rails
2023-08-29 Initial resources structure and content
2023-08-29 Sensors Update
2023-08-30 Completed Power supply schmatic still have to figure out current limit and install potentiometer, and verify buck
2023-08-31 Folder structure layout changes and a begining the board
2023-08-31 Added mcu
2023-09-01 Started laying out relays and current sensors. Working on driving the relays next
2023-09-01 new connector and m2 screws hole
2023-09-01 simple merge
2023-09-01 upload
2023-09-01 access
2023-09-01 change input connector
2023-09-01 exit
2023-09-01 new folder for references
2023-09-01 push of the night
2023-09-02 quick push
2023-09-09 Reworked schematic for more readability and changed symbols from EAGLE to KiCAD.
2023-09-09 Lets gooooo
    h2 Sensor isolation & circuit
2023-09-11 Added logo and assigned parts
2023-09-16 Updated lower amperage relays
2023-09-16 test push
2023-09-16 new kicad prjt
2023-09-16 sch setup
2023-09-16 asdf
2023-09-16 some updates
2023-09-16 mcu placement
2023-09-16 planning
2023-09-16 Lots of updates to relays
2023-09-20 Small revision🐱‍💻
    Actually made it properly 🐱‍💻
2023-09-20 ups
    oops
2023-09-20 Added uart to usb, still needs some work, started prog for mcu
2023-09-21 Actual changes, hopefully merged?
    :anguished:
2023-09-23 quick update
2023-09-23 barebone sch capture done
2023-09-24 👆
    update
2023-09-24 lots of big changes
2023-09-24 Ready to order added all part numbers
2023-09-30 Quick Commit
2023-09-30 cahnges
2023-09-30 Update some Telem
2023-10-07 pushing whatever for new lapto
2023-10-07 add RC filter
2023-10-08 Added Rev 2 Ready to order
2023-10-09 added GPSW and HW DB
2023-10-09 Thats it no more changes
2023-10-12 selected diode
2023-10-14 Telem, FTDI, MCU, CAN
    Added basic components for FTDI, on board telemetry, & CAN transceiver.
    Cleaned up some wiring, added STLink connector with ESD.
2023-10-14 i dont want to get a new laptop
2023-10-14 Big changes to relay board
2023-10-14 adding op-amp
2023-10-14 work sesh 10.14
2023-10-14 added a socket
2023-10-15 Small change
2023-10-21 i dont know whats different
2023-10-21 changes from sat work session
2023-10-22 Started clock config
2023-10-23 Started the PCB design work
2023-10-26 MQ-8 holes slightly larger
    mq-8 de-soldering hopefully won't be a pain?
    silk screen added
2023-10-28 should be jlc ready
    should be within jlc specs
2023-10-28 Board layout is done and routed
2023-10-28 Updated schematic with two 5V buck converters.
2023-10-29 Added Simon board and eddited the dimentions
2023-10-30 Finished the relay board. Once gerbers and drill files are generated we can order from jlc
2023-11-04 Added Current and Voltage sensors for FC power, 12V power, and 5V power.
2023-11-04 Fixed some of the page names and corrected the voltage divider ratios for 12V and 5V voltage sensing.
2023-11-04 current and voltage sensors on board
2023-11-05 op-amp setup
2023-11-05 Humiditiy sensor and other small cahnges
2023-11-05 Started work on the BOM file and I updated the lower current relays to work with 50A models
2023-11-05 Cleaned Up Schmatics Added Headers and OLED and Humidity Sensor Connections
2023-11-06 updated, created gerbers, created p&p, created BOM's
2023-11-07 Started Layout fixed footprint for daughter baord and added M3 mounting holes.
2023-11-09 zener diode change
2023-11-11 voltage sensor divider ckt
2023-11-11 i dont know what im pushing
2023-11-12 Added optocouplers and reworked relay controls
2023-11-12 Added some stuff and cleaned up schmatic also added beeper and heat sink finished placement of power electronics and rough layout of mcu and sensors.
2023-11-12 Made the new gerbs and bom files and ordered the pcb
2023-11-13 started circuitry for the pressure sensor and thermistor on the fuel cell
2023-11-15 Added all required components made modular sensor smaller and and laid out main board
2023-11-16 so much, can't explain
2023-11-16 I am highly sleep deprived
2023-11-17 more things
2023-11-17 pushing some stuff
2023-11-18 pushussy
2023-11-18 new sheet
2023-11-18 changed buttons
2023-11-19 Again too much to say
2023-11-20 Added bulk filter cap and mounting holes for oled
2023-11-20 Most of the schematic done, pcb layout needs DRC
2023-11-20 Changed Bulk caps and added them to LDO out instead of buck
2023-11-20 Fixed holezsx
2023-11-21 So much again
2023-11-23 added outputs
    added 8 i can easily add more later
2023-11-23 i dont know what this is
2023-11-24 things
2023-11-24 I really shouldn't be pushing so much but oh well
2023-11-25 pushy push
2023-11-25 output caps, low pass filters, 3 bucks
2023-11-25 other stuff
2023-11-26 Push latest changes.
2023-11-26 Finished
2023-11-26 I may have broke the repo?
2023-11-26 added inrush current limiting cap and changed buck out voltage selection voltage divider resistors to standard values
2023-11-26 shit forgot to save
2023-11-26 Making changes
2023-11-26 Updated pcb DRC
2023-11-26 fixzed some stuffs
2023-11-26 Fixed some stuffs
2023-11-27 added inductor
2023-11-27 i believe everything is ready for mcu
2023-11-28 op amps on the current sens outputs
2023-11-29 added some mcu stuff, need to configure
2023-11-29 Major rework, left some comments
2023-11-29 Made some changes to the SWD
2023-11-29 firmware, and mcu done?????
2023-12-01 hhhhhhhh
2023-12-02 doN:
2023-12-02 progress from today
2023-12-02 lots of changes, pcb ready for order
2023-12-03 Major changes: removed 12V reg, added battery power for 5V/12V, revised current sensing modules to have a smaller upper limit, added voltage divider + op-amp for more measurements.
2023-12-07 made changes to Power flow stuff
2023-12-18 Started the code
2023-12-21 Big code
2023-12-22 beginning stages of fuel cell control loop
2024-01-01 latest changes
2024-01-01 pushing what ive done
2024-01-01 stuff
2024-01-01 UPdated capacitor ftp and something else dont remember
2024-01-03 added a bunch of footprints and other stuff...
2024-01-05 added a bunch of foot prints and 3d models
2024-01-06 i think schematic is done??
2024-01-06 schematic done??
2024-01-06 some stuff
2024-01-10 idk what this is :P
2024-01-10 made changes to schematic
2024-01-10 no more global variables
2024-01-12 some of the touch ups
2024-01-13 Started the code for the relay board
2024-01-13 everything but the battery input done
2024-01-13 everthing so far
2024-01-13 everything
2024-01-13 some small changes
2024-01-13 better datasheet
2024-01-13 battery con footprint better
2024-01-13 this
2024-01-13 everything done?!
2024-01-15 i commit way too much
2024-01-16 changes?
2024-01-23 Added bucks and fixed pinouts
2024-01-24 route-Breakout-board
2024-01-27 something
2024-01-27 fireware
2024-01-28 board-final-draft
2024-01-29 gerber files added
2024-01-30 All values calculated, next step is to pick parts.
2024-01-31 trying to implement a cmake version
2024-02-01 Picked most of the parts except for some resistors
2024-02-01 Some jlc stuff
2024-02-01 writing some more code in my new awesomeide
2024-02-02 PCB started
2024-02-02 Reworking the schematic and updating symbols with footprints. Added symbol & ftp library from the battery power board to aid in development
2024-02-02 just consistency
2024-02-03 Began PCB layout.
2024-02-03 Routed PCB except for battery 5V
2024-02-03 moved james pcb to another folder so we can do rev 2 of the layout, changed some footprints to be consistent with kicad, changed the inductor to a smaller bit similar package with certain characteris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
2024-02-03 James PCB folder updated with current rev. Still need to figure out how to route the MCU.
2024-02-03 Most recent PCB routing, everything except for MCU and 5V battery power is routed.
2024-02-04 updated schematic slightly
2024-02-05 started rework
2024-02-05 Routed PCB.
2024-02-06 Reworked mcu layout for caps, reworked ftdi chip layout, reworked lots of other things too
2024-02-06 consistency
2024-02-06 final
2024-02-08 Final revision of routed PCB from James. Still need silkscreen logo
2024-02-11 Got adc working with rtos
2024-02-12 Fixed ADC timings, H2 and temp should be able to be updated reliably
2024-02-15 firmware stufff
2024-02-18 last known working code
2024-02-19 Last working code
2024-02-19 finished up pcb
2024-02-20 Added bme and lccd working
2024-02-22 Fuel controller code is almost at its base operating point. Pressure and temp sensor still needs to be tested, otherwise, getting close to a working point
2024-02-22 ADC working properly, able to receive relay configuration commands and respond. Succesfully transmitting cap voltage as well
2024-02-26 Made some changes
2024-02-27 Added a .gitignore so that the build folder and compile_commands.json symbolic link doesn't get added
2024-03-02 some firmware
2024-03-02 firmware progress
2024-03-02 The firmware plan
2024-03-06 copied nick
2024-03-09 done layout v2
2024-03-09 For griffy
2024-03-09 Pushing some firmware stuff
2024-03-12 Got rf bridge working
2024-03-14 Removed different version of source code and renamed the main src code folder
2024-03-16 Missed something
2024-03-16 stashing
2024-03-16 Git doesn't push empty folders?
2024-03-16 cleaned it up a bit
2024-03-16 ADC!!
2024-03-16 Started up the code configs for fcpb
2024-03-16 some can stuff
2024-03-16 closed stm
2024-03-16 fixed ioc
2024-03-17 got the can transmitting
2024-03-19 Re-adjusted the can handling threads and callbacks
2024-03-19 Adjusted can
2024-03-23 Changed the code and fixed the file structure
2024-03-23 More overhaul on the code
2024-03-26 start dashboard folder
2024-03-28 start prjt
2024-04-05 some gui stuff
2024-04-05 a little update, should be able to read the internally stored data now
2024-04-06 untested code
2024-04-25 This version of the board/code was used at comp
2024-04-25 Some changes to the code were made at comp, they are in this push
2024-05-12 added README
2024-05-12 Renamed README
2024-09-14 some code that was change
2025-01-04 Added CAN
2025-01-05 RF working and sending CAN
2025-01-05 Added seperate send project
2025-01-05 Added RTC
2025-01-05 Added rssi and snr and coding rate and ldo flag and ocp and bandwoidth
2025-01-06 Not working
2025-01-06 RF working better and can was under volting so fixed that
2025-02-15 idk what this is
2025-03-13 new code for potentially using old rb with new system
